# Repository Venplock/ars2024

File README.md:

# ars2024
Automated Resistor Sorter

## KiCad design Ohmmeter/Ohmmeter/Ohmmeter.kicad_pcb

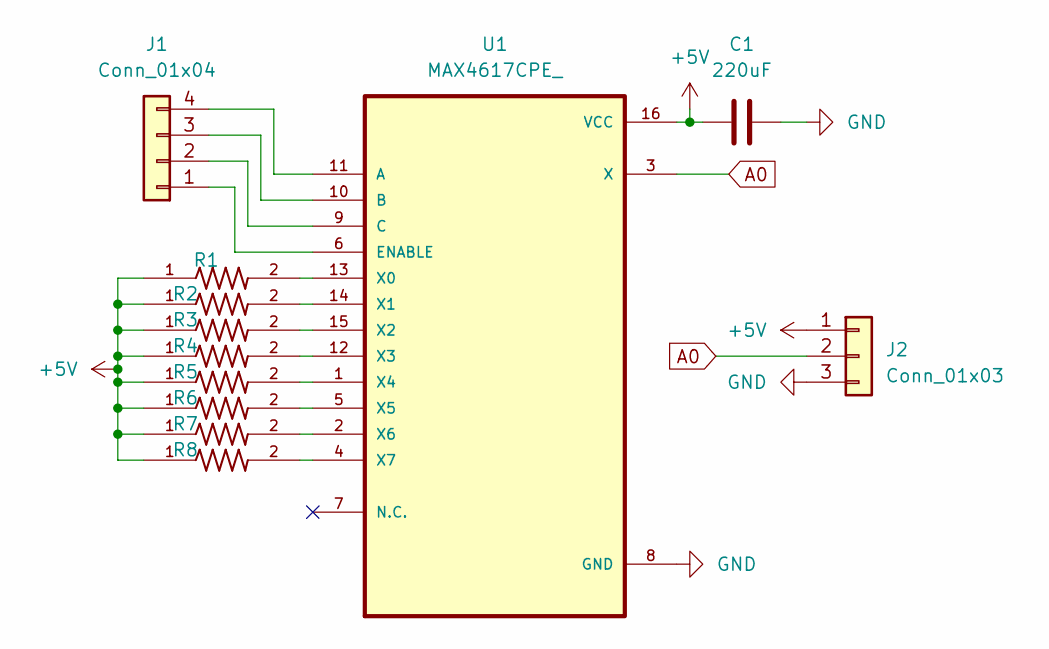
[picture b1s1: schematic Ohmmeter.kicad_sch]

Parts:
C1: 220uF; C_Radial_D5.0mm_H11.0mm_P2.00mm
J1: Conn_01x04; PinSocket_1x04_P2.54mm_Vertical
J2: Conn_01x03; PinHeader_1x03_P2.54mm_Vertical
R1, R2, R3, R4, R5, R6, R7, R8: RC0603JR-071KL; R_Axial_DIN0204_L3.6mm_D1.6mm_P5.08mm_Horizontal
U1: MAX4617CPE_; DIP794W47P254L1943H457Q16

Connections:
+5V: C1.1, J2.1, R1.1, R2.1, R3.1, R4.1, R5.1, R6.1, R7.1, R8.1, U1.16 (VCC)
A0: J2.2, U1.3 (X)
GND: C1.2, J2.3, U1.8 (GND)
unnamed: J1.1, U1.6 (ENABLE)
unnamed: J1.2, U1.9 (C)
unnamed: J1.3, U1.10 (B)
unnamed: J1.4, U1.11 (A)
unnamed: R1.2, U1.13 (X0)
unnamed: R2.2, U1.14 (X1)
unnamed: R3.2, U1.15 (X2)
unnamed: R4.2, U1.12 (X3)
unnamed: R5.2, U1.1 (X4)
unnamed: R6.2, U1.5 (X5)
unnamed: R7.2, U1.2 (X6)
unnamed: R8.2, U1.4 (X7)

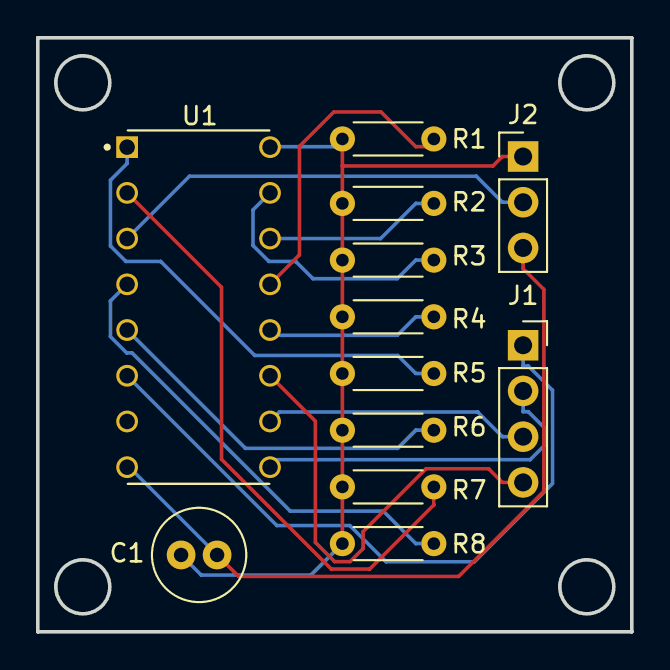
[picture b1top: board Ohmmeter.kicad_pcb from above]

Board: 2 copper layers, 33.0 x 33.0 mm, 12 parts (0 on the bottom side), 15 nets.

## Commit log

2024-04-29 Add files via upload
    Arduino Code
2024-04-29 Rename arm_control.ino to Arm Module/arm_control.ino
2024-12-06 Rename main.cpp to Raspberry Pi/main.cpp
